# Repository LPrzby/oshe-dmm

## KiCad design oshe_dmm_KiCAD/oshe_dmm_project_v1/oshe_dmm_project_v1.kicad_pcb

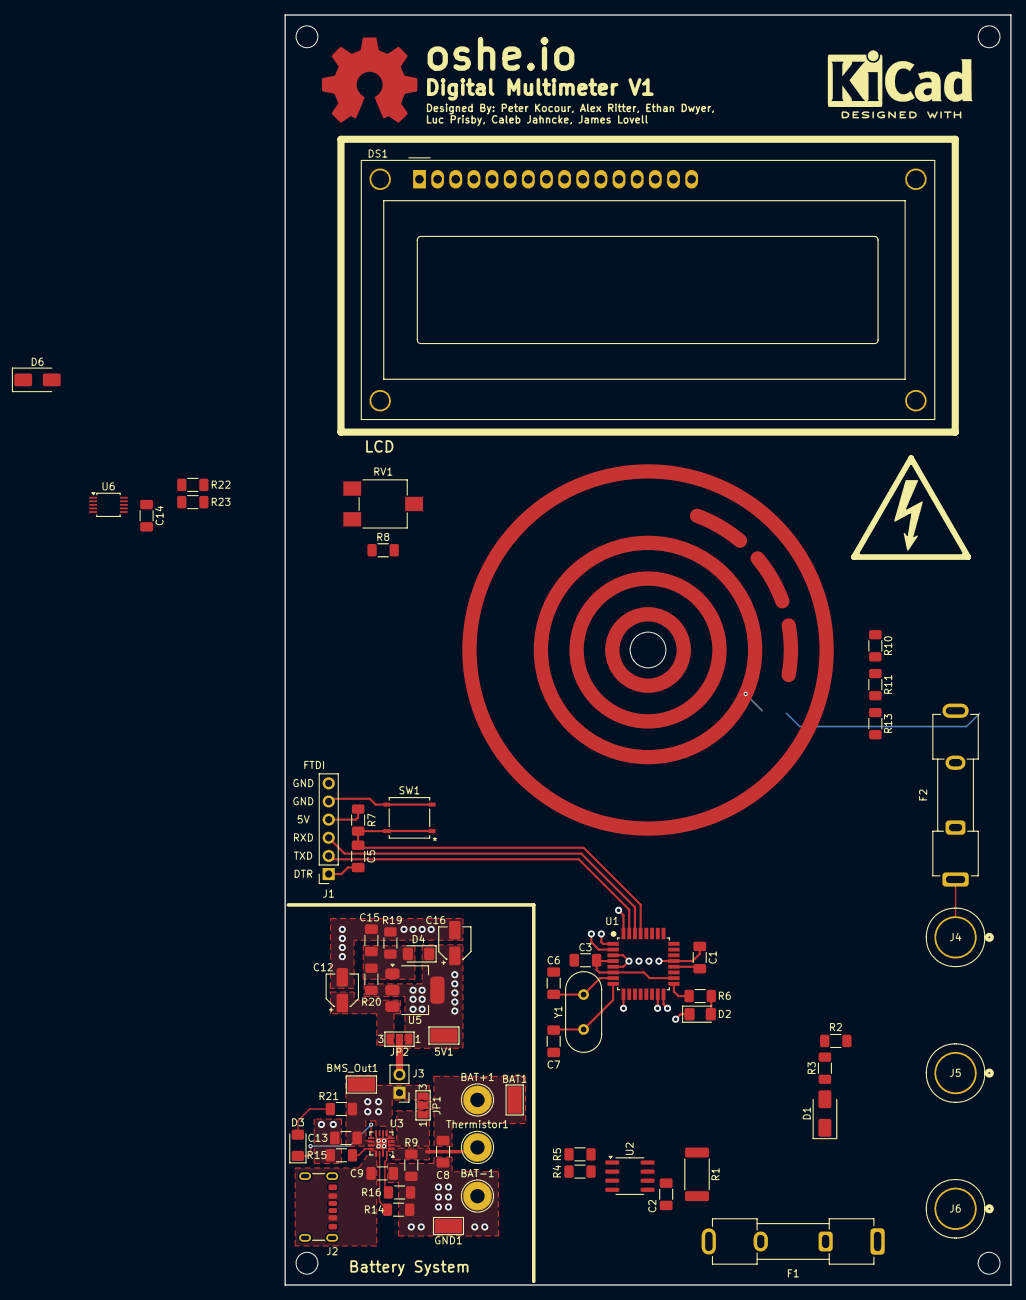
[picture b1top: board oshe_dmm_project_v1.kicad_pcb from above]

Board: 4 copper layers, 101.6 x 177.8 mm, 64 parts (0 on the bottom side), 44 nets.

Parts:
5V1: TestPoint; TestPoint_Keystone_5019_Minature
BAT1: TestPoint; TestPoint_Keystone_5019_Minature
BAT+1: Pad; TestPoint_THTPad_D4.0mm_Drill2.0mm
BAT-1: Pad; TestPoint_THTPad_D4.0mm_Drill2.0mm
BMS_Out1: TestPoint; TestPoint_Keystone_5019_Minature
C1, C2, C3, C5: 0.1uF; C_1206_3216Metric_Pad1.33x1.80mm_HandSolder
C6, C7: 22pF; C_1206_3216Metric_Pad1.33x1.80mm_HandSolder
C8, C9, C13, C15: 10uF; C_1206_3216Metric_Pad1.33x1.80mm_HandSolder
C12, C16: 1uF; CP_Elec_4x4.5
C14: 100nF; C_1206_3216Metric_Pad1.33x1.80mm_HandSolder
D1, D6: SMAJ200CA; D_SMA
D2: Green; LED_1206_3216Metric_Pad1.42x1.75mm_HandSolder
D3: CHG; LED_1206_3216Metric_Pad1.42x1.75mm_HandSolder
D4: 1N4002; D_1206_3216Metric_Pad1.42x1.75mm_HandSolder
DS1: WC1602A
F1: 5A; Fuseholder_Clip-5x20mm_Keystone_3512P_Inline_P23.62x7.27mm_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
F2: 500mA; Fuseholder_Clip-5x20mm_Keystone_3512P_Inline_P23.62x7.27mm_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
GND1: TestPoint; TestPoint_Keystone_5019_Minature
J1: FTDI Basic; PinSocket_1x06_P2.54mm_Vertical
J2: USB_C_Receptacle_PowerOnly_6P; USB_C_Receptacle_GCT_USB4125-xx-x-0190_6P_TopMnt_Horizontal
J3: ON/OFF; PinHeader_1x02_P2.54mm_Vertical
J4: Voltage; CONN_575-8_KEY
J5: GND; CONN_575-8_KEY
J6: Current; CONN_575-8_KEY
JP1, JP2: SolderJumper; SolderJumper-3_P1.3mm_Open_Pad1.0x1.5mm_NumberLabels
R1: 0.064; R_2512_6332Metric_Pad1.40x3.35mm_HandSolder
R2: R_US; R_1206_3216Metric_Pad1.30x1.75mm_HandSolder
R3, R7, R9, R13, R22, R23: 10k; R_1206_3216Metric_Pad1.30x1.75mm_HandSolder
R4, R5: 1k; R_1206_3216Metric_Pad1.30x1.75mm_HandSolder
R6: 330; R_1206_3216Metric_Pad1.30x1.75mm_HandSolder
R8: 220K; R_1206_3216Metric_Pad1.30x1.75mm_HandSolder
R10: 900K; R_1206_3216Metric_Pad1.30x1.75mm_HandSolder
R11: 90k; R_1206_3216Metric_Pad1.30x1.75mm_HandSolder
R14: 0; R_1206_3216Metric_Pad1.30x1.75mm_HandSolder
R15, R21: 1.5k; R_1206_3216Metric_Pad1.30x1.75mm_HandSolder
R16: 1.78k; R_1206_3216Metric_Pad1.30x1.75mm_HandSolder
R19: 1.2k; R_1206_3216Metric_Pad1.30x1.75mm_HandSolder
R20: 390; R_1206_3216Metric_Pad1.30x1.75mm_HandSolder
RV1: 10k; Potentiometer_ACP_CA6-VSMD_Vertical
SW1: PTS526 SK15 SMTR2 LFS; SMT_FS
Thermistor1: Pad; TestPoint_THTPad_D4.0mm_Drill2.0mm
U1: ATmega328P-A; TQFP-32_7x7mm_P0.8mm
U2: INA219BxD; SOIC-8_3.9x4.9mm_P1.27mm
U3: BQ24075RGT; VQFN-16-1EP_3x3mm_P0.5mm_EP1.6x1.6mm
U5: LM317_SOT-223; SOT-223-3_TabPin2
U6: ADS1115IDGS; TSSOP-10_3x3mm_P0.5mm
Y1: 16MHz; Crystal_HC49-U_Vertical

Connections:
9V_BAT_IN: BMS_Out1.1, C13.1, J3.1, JP1.3 (B), R21.1, U3.5 (EN2), U3.10 (OUT), U3.11 (OUT)
+5V: 5V1.1, C2.2, C3.1, C14.1, C16.1, D4.1 (K), DS1.2 (VDD), J1.4, JP2.1 (A), R7.2, R8.1, R20.1, R22.1, R23.1, RV1.1, U1.4 (VCC), U1.6 (VCC), U1.18 (AVCC), U2.5 (VS), U5.2 (VO), U6.8 (VDD)
/2V: D6.2 (A2), F2.2, R10.1
/20V: R10.2, R11.1
/200V: R11.2, R13.1
/R-ILIM: R15.1, U3.12 (ILIM)
/R-ISET: R16.1, U3.16 (ISET)
BMS_BAT_IN: JP1.1 (A), U3.2 (BAT), U3.3 (BAT)
Current_Input: F1.1, J6.1
D2: DS1.14 (D7), U1.32 (PD2)
D3: DS1.13 (D6), U1.1 (PD3)
D4: DS1.12 (D5), U1.2 (PD4)
D5: DS1.11 (D4), U1.9 (PD5)
DTR: C5.2, J1.1
GND: BAT-1.1, C1.1, C2.1, C3.2, C6.2, C7.1, C8.2, C9.2, C12.2, C13.2, C14.2, C15.2, C16.2, D2.1 (K), DS1.1 (VSS), DS1.5 (R/W), DS1.16 (LED(-)), GND1.1, J1.5, J1.6, J2.A12 (GND), J2.B12 (GND), J2.S1 (SHIELD), R4.1, R5.1, R9.2, R14.2, R15.2, R16.2, R19.2, RV1.3, SW1.3, SW1.4, U1.3 (GND), U1.5 (GND), U1.21 (GND), U2.6 (GND), U3.4 (~CE), U3.6 (EN1), U3.8 (VSS), U3.15 (SYSOFF), U3.17 (VSS), U6.1 (ADDR), U6.3 (GND)
Input_Negative: D6.1 (A1), J5.1, R1.2, R13.2, U2.7 (IN-), U6.5 (AIN1)
MISO/D12: DS1.6 (E), U1.16 (PB4)
MOSI/D11: DS1.4 (RS), U1.15 (PB3)
unnamed: D1.2 (A2), R2.2, R3.1
unnamed: D2.2 (A), R6.1
unnamed: D3.2 (A), R21.2
unnamed: D3.1 (K), U3.9 (~CHG)
unnamed: C15.1, D4.2 (A), R19.1, R20.2, U5.1 (ADJ)
unnamed: DS1.15 (LED(+)), R8.2
unnamed: DS1.3 (VO), RV1.2
unnamed: J3.2, JP2.2 (C)
unnamed: BAT1.1, BAT+1.1, C8.1, JP1.2 (C)
unnamed: C12.1, JP2.3 (B), U5.3 (VI)
unnamed: C1.2, U1.20 (AREF)
unnamed: C6.1, U1.7 (XTAL1/PB6), Y1.2
unnamed: C7.2, U1.8 (XTAL2/PB7), Y1.1
unnamed: C5.1, R7.1, SW1.1, SW1.2, U1.29 (~RESET/PC6)
unnamed: R4.2, U2.2 (A0)
unnamed: R5.2, U2.1 (A1)
unnamed: F1.2, R1.1, U2.8 (IN+)
unnamed: R14.1, U3.14 (TMR)
RXD: J1.3, U1.30 (PD0)
SCK/D13: R6.2, U1.17 (PB5)
SCL: R22.2, U1.28 (PC5), U2.4 (SCL), U6.10 (SCL)
SDA: R23.2, U1.27 (PC4), U2.3 (SDA), U6.9 (SDA)
TS: R9.1, Thermistor1.1, U3.1 (TS)
TXD: J1.2, U1.31 (PD1)
USB_Power_IN: C9.1, J2.A9 (VBUS), J2.B9 (VBUS), U3.13 (IN)
Voltage_Input: F2.1, J4.1

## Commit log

2025-03-08 began current setting
    Current switch setting ring added
2025-03-09 Rings ~70% done
    updated rings, to be completed tonight
